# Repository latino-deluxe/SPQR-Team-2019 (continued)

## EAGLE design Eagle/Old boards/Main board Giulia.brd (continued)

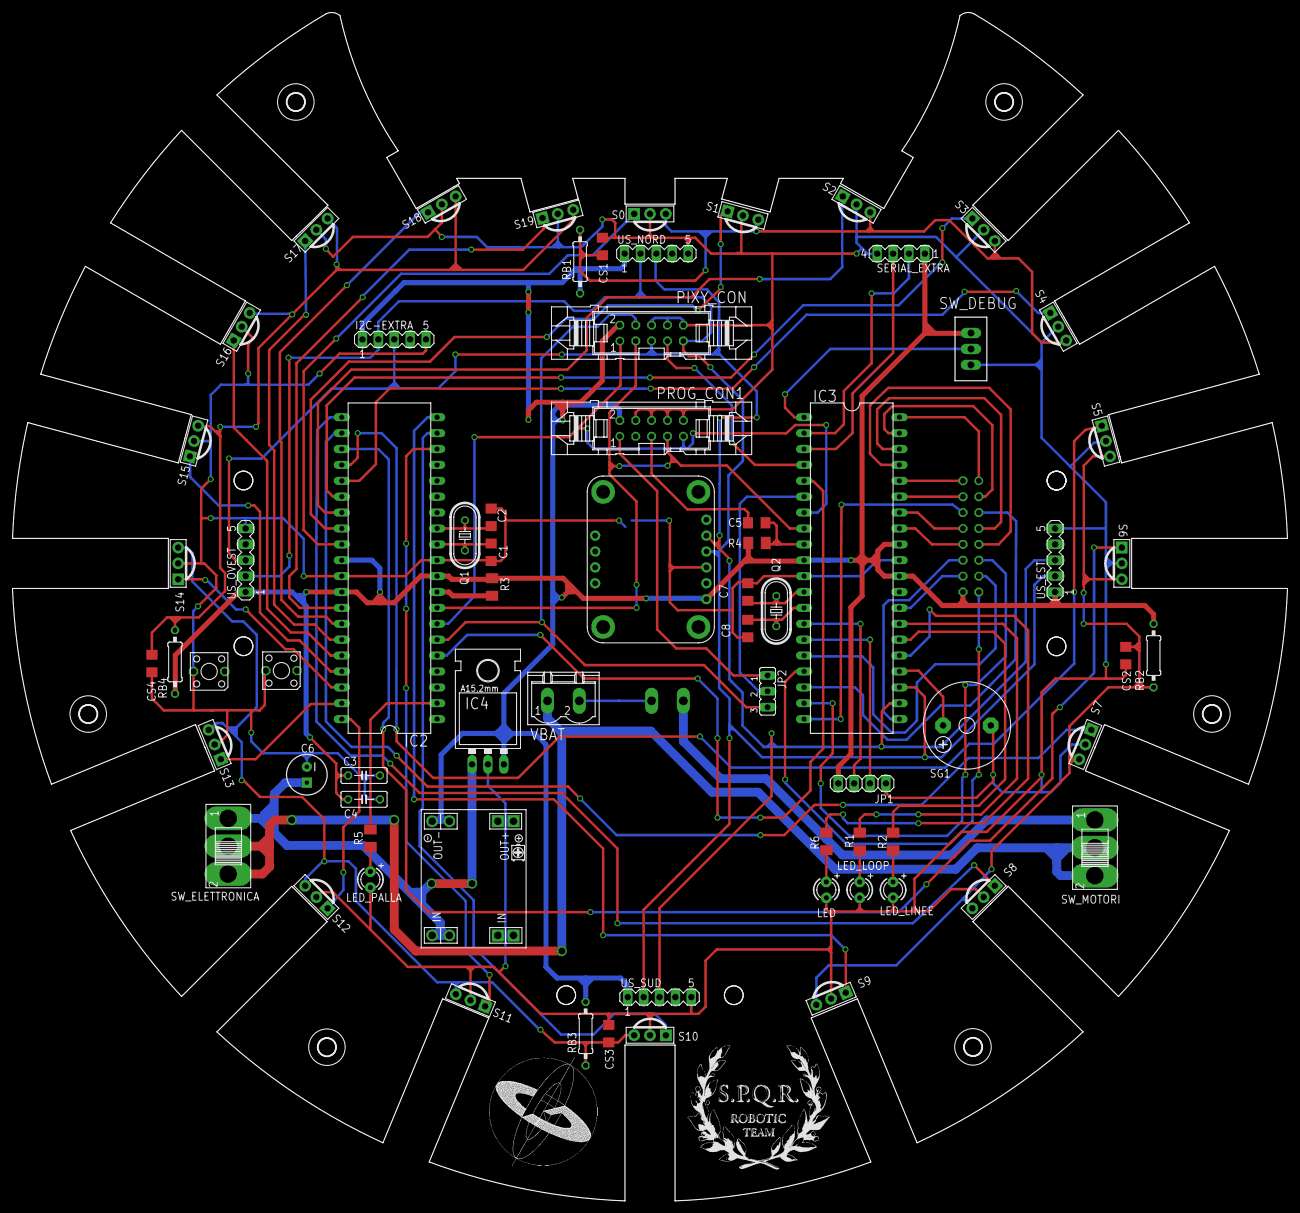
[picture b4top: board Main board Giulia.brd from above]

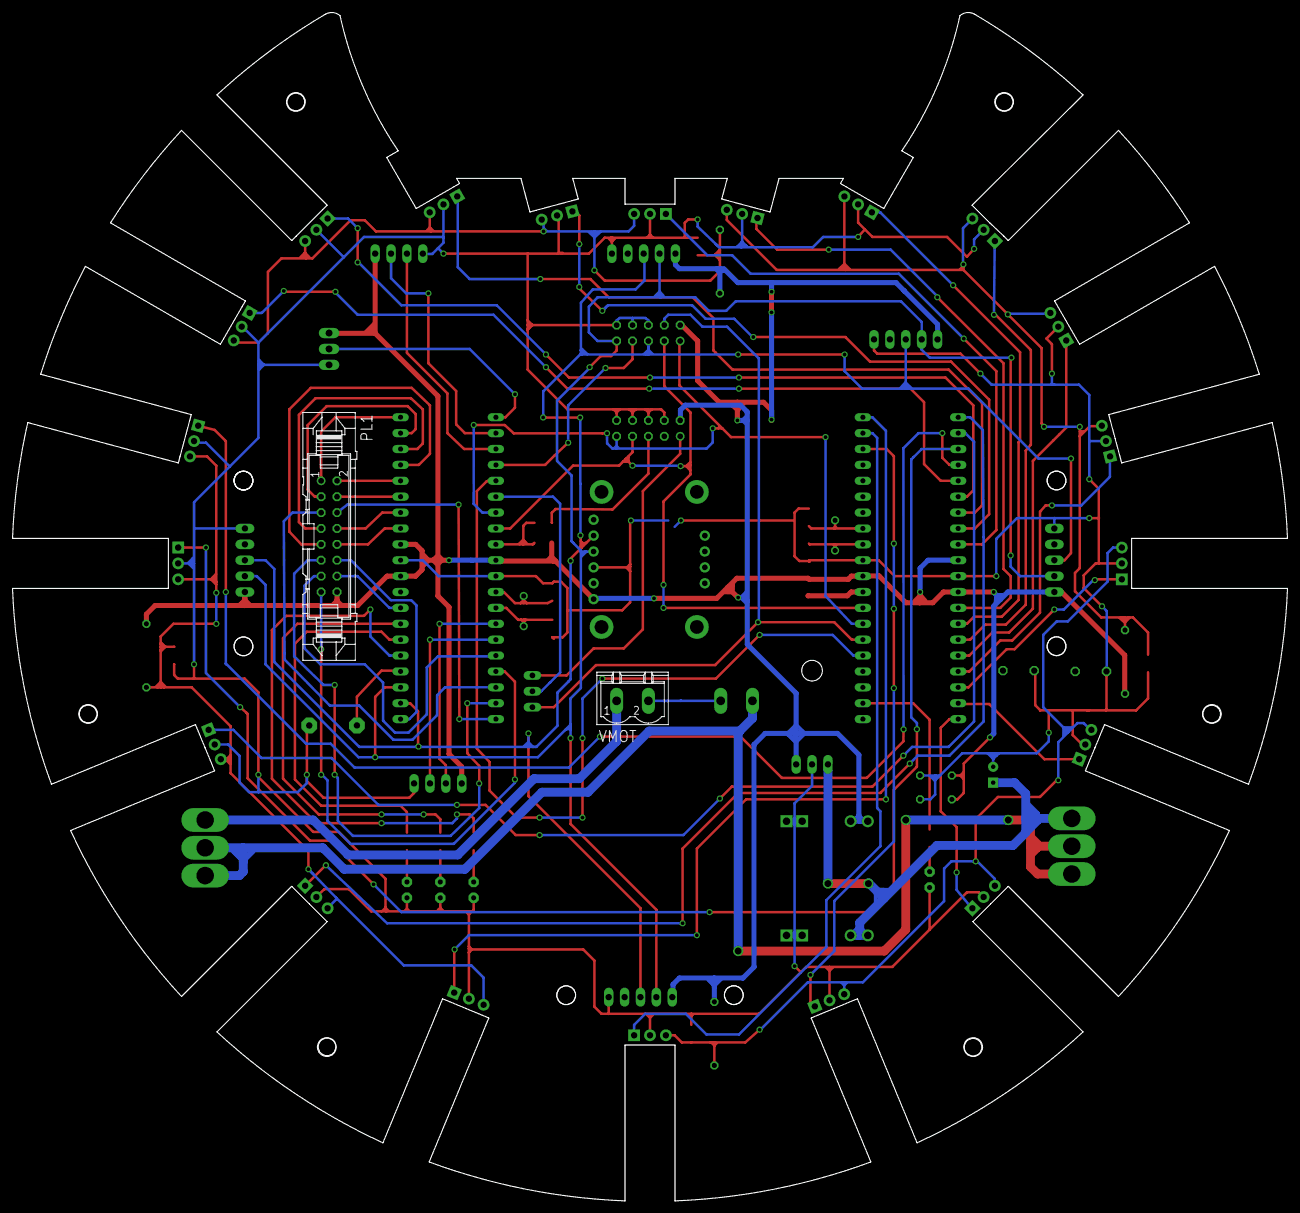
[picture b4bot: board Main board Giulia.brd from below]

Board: 2 copper layers, 203.8 x 190.0 mm, 78 parts (2 on the bottom side), 74 nets.

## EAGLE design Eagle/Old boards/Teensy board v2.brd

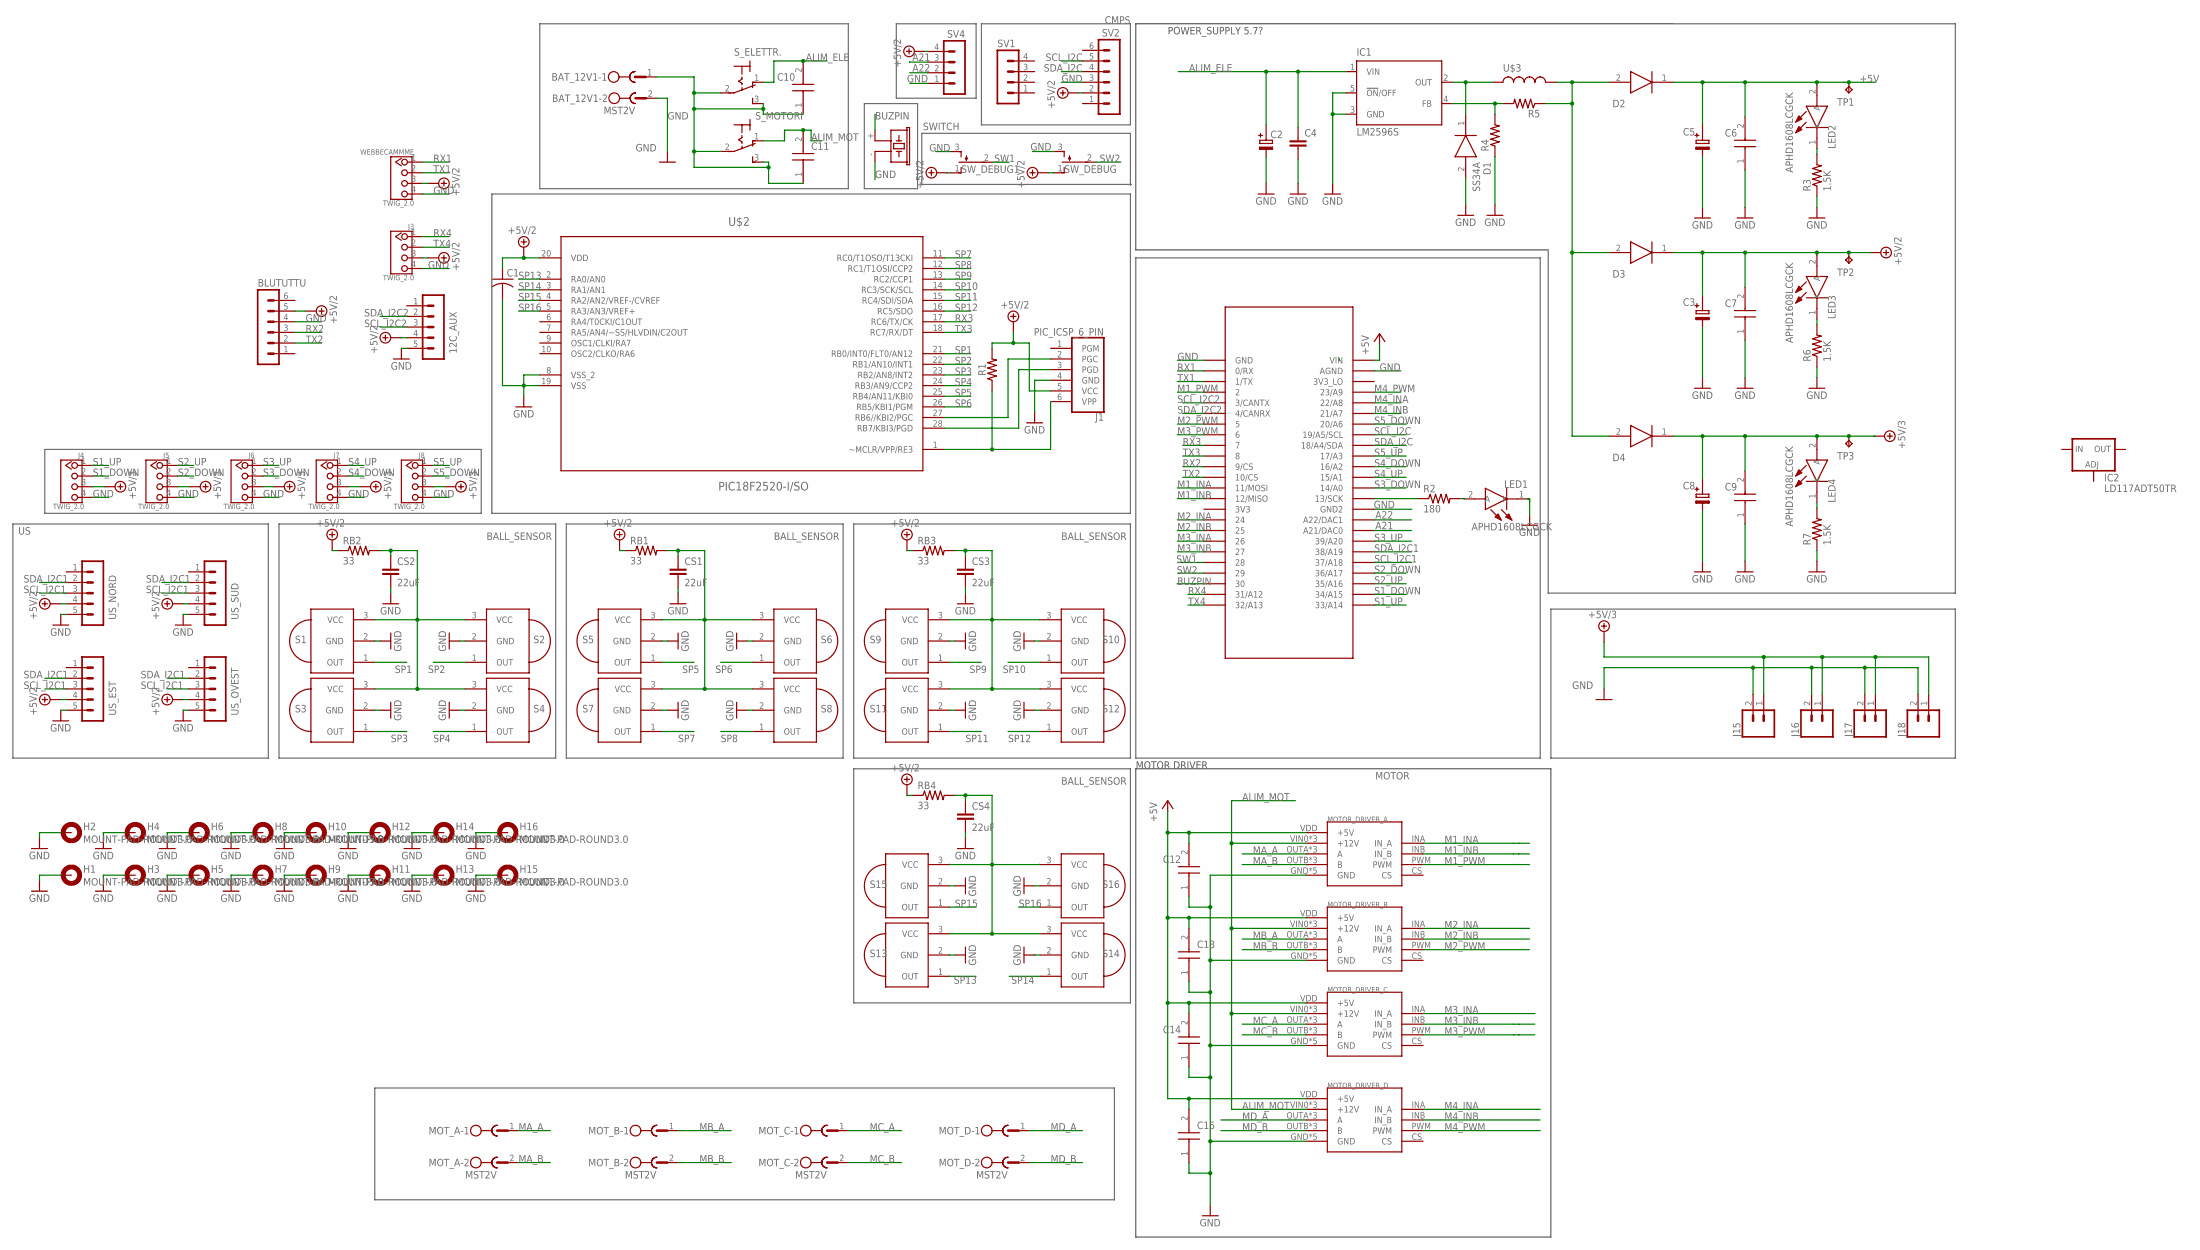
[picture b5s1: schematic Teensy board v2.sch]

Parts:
12C_AUX: MA05-1
BAT_12V1: MST2V; MSTBV2
BLUTUTTU: MA06-1
C1: C-USC1206; C1206
C2, C3, C5, C8: C-PR-SMD-SV-E/F; SV-E/F
C4: CC1206; C1206
C6, C7, C9, C10, C11, C12, C13, C14, C15: 12065D106KAT2A; CAPC3216X229N
CS1, CS2, CS3, CS4: 22uF; C1206
D1: SS34A; DIOM5026X262N
D2, D3, D4: SE20FG-M3_H; SODFL3718X108N
H1, H2, H3, H4, H5, H6, H7, H8, H9, H10, H11, H12, H13, H14, H15, H16: MOUNT-PAD-ROUND3.0; 3,0-PAD
IC1: LM2596S; TO263-5
IC2: LD117ADT50TR; DPACK
J1: PIC_ICSP_6_PIN; MOLEX-1X6
J3, J4, J5, J6, J7, J8: TWIG_2.0; 2.0_1X4
J15, J16, J17, J18: CONN_02; 1X02
LED1, LED2, LED3, LED4: APHD1608LCGCK; LEDM168X80N
MOTOR_DRIVER_A: VNH5019
MOTOR_DRIVER_B: VNH5019
MOTOR_DRIVER_C: VNH5019
MOTOR_DRIVER_D: VNH5019
MOT_A: MST2V; MSTBV2
MOT_B: MST2V; MSTBV2
MOT_C: MST2V; MSTBV2
MOT_D: MST2V; MSTBV2
R1: 10k; M1206
R2: 180; M1206
R3, R6, R7: 1.5K; R1206
R4, R5: R-US_R1206; R1206
RB1, RB2, RB3, RB4: 33; M1206
S1, S2, S3, S4, S5, S6, S7, S8, S9, S10, S11, S12, S13, S14, S15, S16: PNA460XM
SG1: F/CM12P
SV1, SV4: MA04-1
SV2: MA06-1
SW_DEBUG, SW_DEBUG1: TL38PO; TL3XPO
S_ELETTR.: 320-916
S_MOTORI: 320-916
TP1, TP2, TP3: TPTP13SQ; TP13SQ
U$1: TEENSY_3.5/3.6
U$2: PIC18F2520-I/SO; SOIC127P1030X265-28N
U$3: MSS1260
US_EST: MA05-1
US_NORD: MA05-1
US_OVEST: MA05-1
US_SUD: MA05-1
WEBBECAMMME: TWIG_2.0; 2.0_1X4

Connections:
5.7V-DIRAMAZIONE2: D2.2 (A), D3.2 (A), D4.2 (A), R5.1, U$3.P$1
+5V: C5.+, C6.2, D2.1 (K), LED2.2 (A), TP1.TP, U$1.VIN
+5V/2: 12C_AUX.4, BLUTUTTU.5, C1.1, C3.+, C7.2, D3.1 (K), J1.5 (VCC), J3.3, LED3.2 (A), R1.2, RB1.1, RB2.1, RB3.1, RB4.1, SV2.2, SV4.4, SW_DEBUG.1 (O), SW_DEBUG1.1 (O), TP2.TP, U$2.20 (VDD), US_EST.4, US_NORD.4, US_OVEST.4, US_SUD.4, WEBBECAMMME.3
+5V/3: C8.+, C9.2, D4.1 (K), J4.3, J5.3, J6.3, J7.3, J8.3, J15.1, J16.1, J17.1, J18.1, LED4.2 (A), TP3.TP
A21: SV4.3, U$1.21/DAC0 (A21/DAC0)
A22: SV4.2, U$1.A22/DAC1
ALIM_ELE: C2.+, C4.1, C10.2, IC1.1 (VIN), S_ELETTR..1 (O)
ALIM_MOT: C11.2, MOTOR_DRIVER_A.VIN0 (+12V), MOTOR_DRIVER_A.VIN1 (+12V), MOTOR_DRIVER_A.VIN2 (+12V), MOTOR_DRIVER_B.VIN0 (+12V), MOTOR_DRIVER_B.VIN1 (+12V), MOTOR_DRIVER_B.VIN2 (+12V), MOTOR_DRIVER_C.VIN0 (+12V), MOTOR_DRIVER_C.VIN1 (+12V), MOTOR_DRIVER_C.VIN2 (+12V), MOTOR_DRIVER_D.VIN0 (+12V), MOTOR_DRIVER_D.VIN1 (+12V), MOTOR_DRIVER_D.VIN2 (+12V), S_MOTORI.1 (O)
BUZPIN: SG1.+ (1), U$1.30
GND: 12C_AUX.5, BAT_12V1.2, BLUTUTTU.4, C1.2, C2.-, C3.-, C4.2, C5.-, C6.1, C7.1, C8.-, C9.1, C12.1, C13.1, C14.1, C15.1, CS1.2, CS2.2, CS3.2, CS4.2, D1.2 (A), H1.B3,0, H2.B3,0, H3.B3,0, H4.B3,0, H5.B3,0, H6.B3,0, H7.B3,0, H8.B3,0, H9.B3,0, H10.B3,0, H11.B3,0, H12.B3,0, H13.B3,0, H14.B3,0, H15.B3,0, H16.B3,0, IC1.3 (GND), IC1.5 (!ON!/OFF), J1.4 (GND), J3.4, J4.4, J5.4, J6.4, J7.4, J8.4, J15.2, J16.2, J17.2, J18.2, LED1.1 (K), MOTOR_DRIVER_A.GND, MOTOR_DRIVER_A.GND0 (GND), MOTOR_DRIVER_A.GND1 (GND), MOTOR_DRIVER_A.GND2 (GND), MOTOR_DRIVER_A.GND3 (GND), MOTOR_DRIVER_B.GND, MOTOR_DRIVER_B.GND0 (GND), MOTOR_DRIVER_B.GND1 (GND), MOTOR_DRIVER_B.GND2 (GND), MOTOR_DRIVER_B.GND3 (GND), MOTOR_DRIVER_C.GND, MOTOR_DRIVER_C.GND0 (GND), MOTOR_DRIVER_C.GND1 (GND), MOTOR_DRIVER_C.GND2 (GND), MOTOR_DRIVER_C.GND3 (GND), MOTOR_DRIVER_D.GND, MOTOR_DRIVER_D.GND0 (GND), MOTOR_DRIVER_D.GND1 (GND), MOTOR_DRIVER_D.GND2 (GND), MOTOR_DRIVER_D.GND3 (GND), R3.1, R4.1, R6.1, R7.1, S1.2 (GND), S2.2 (GND), S3.2 (GND), S4.2 (GND), S5.2 (GND), S6.2 (GND), S7.2 (GND), S8.2 (GND), S9.2 (GND), S10.2 (GND), S11.2 (GND), S12.2 (GND), S13.2 (GND), S14.2 (GND), S15.2 (GND), S16.2 (GND), SG1.- (2), SV2.3, SV4.1, SW_DEBUG.3 (S), SW_DEBUG1.3 (S), U$1.AGND, U$1.GND, U$1.GND2, U$2.8 (VSS_2), U$2.19 (VSS), US_EST.5, US_NORD.5, US_OVEST.5, US_SUD.5, WEBBECAMMME.4
M1_INA: MOTOR_DRIVER_A.INA (IN_A), U$1.11/MOSI
M1_INB: MOTOR_DRIVER_A.INB (IN_B), U$1.12/MISO
M1_PWM: MOTOR_DRIVER_A.PWM, U$1.2
M2_INA: MOTOR_DRIVER_B.INA (IN_A), U$1.24
M2_INB: MOTOR_DRIVER_B.INB (IN_B), U$1.25
M2_PWM: MOTOR_DRIVER_B.PWM, U$1.5
M3_INA: MOTOR_DRIVER_C.INA (IN_A), U$1.26
M3_INB: MOTOR_DRIVER_C.INB (IN_B), U$1.27
M3_PWM: MOTOR_DRIVER_C.PWM, U$1.6
M4_INA: MOTOR_DRIVER_D.INA (IN_A), U$1.22/A8
M4_INB: MOTOR_DRIVER_D.INB (IN_B), U$1.21/A7
M4_PWM: MOTOR_DRIVER_D.PWM, U$1.23/A9
MA_A: MOTOR_DRIVER_A.OUTA (A), MOTOR_DRIVER_A.OUTA2 (A), MOTOR_DRIVER_A.OUTA3 (A), MOT_A.1
MA_B: MOTOR_DRIVER_A.OUTB (B), MOTOR_DRIVER_A.OUTB1 (B), MOTOR_DRIVER_A.OUTB3 (B), MOT_A.2
MB_A: MOTOR_DRIVER_B.OUTA (A), MOTOR_DRIVER_B.OUTA2 (A), MOTOR_DRIVER_B.OUTA3 (A), MOT_B.1
MB_B: MOTOR_DRIVER_B.OUTB (B), MOTOR_DRIVER_B.OUTB1 (B), MOTOR_DRIVER_B.OUTB3 (B), MOT_B.2
MC_A: MOTOR_DRIVER_C.OUTA (A), MOTOR_DRIVER_C.OUTA2 (A), MOTOR_DRIVER_C.OUTA3 (A), MOT_C.1
MC_B: MOTOR_DRIVER_C.OUTB (B), MOTOR_DRIVER_C.OUTB1 (B), MOTOR_DRIVER_C.OUTB3 (B), MOT_C.2
MD_A: MOTOR_DRIVER_D.OUTA (A), MOTOR_DRIVER_D.OUTA2 (A), MOTOR_DRIVER_D.OUTA3 (A), MOT_D.1
MD_B: MOTOR_DRIVER_D.OUTB (B), MOTOR_DRIVER_D.OUTB1 (B), MOTOR_DRIVER_D.OUTB3 (B), MOT_D.2
unnamed: J1.6 (VPP), R1.1, U$2.1 (~MCLR/VPP/RE3)
unnamed: J1.3 (PGD), U$2.28 (RB7/KBI3/PGD)
unnamed: J1.2 (PGC), U$2.27 (RB6//KBI2/PGC)
unnamed: R2.1, U$1.13/SCK
unnamed: LED1.2 (A), R2.2
unnamed: C12.2, C13.2, C14.2, C15.2, D1.1 (K), IC1.2 (OUT), MOTOR_DRIVER_A.VDD (+5V), MOTOR_DRIVER_B.VDD (+5V), MOTOR_DRIVER_C.VDD (+5V), MOTOR_DRIVER_D.VDD (+5V), U$3.P$2
unnamed: IC1.4 (FB), R4.2, R5.2
unnamed: LED2.1 (K), R3.2
unnamed: LED3.1 (K), R6.2
unnamed: LED4.1 (K), R7.2
unnamed: BAT_12V1.1, C10.1, C11.1, S_ELETTR..2, S_ELETTR..3 (S), S_MOTORI.2, S_MOTORI.3 (S)
POWER_BLOK_1: CS1.1, RB1.2, S5.3 (VCC), S6.3 (VCC), S7.3 (VCC), S8.3 (VCC)
POWER_BLOK_2: CS2.1, RB2.2, S1.3 (VCC), S2.3 (VCC), S3.3 (VCC), S4.3 (VCC)
POWER_BLOK_3: CS3.1, RB3.2, S9.3 (VCC), S10.3 (VCC), S11.3 (VCC), S12.3 (VCC)
POWER_BLOK_4: CS4.1, RB4.2, S13.3 (VCC), S14.3 (VCC), S15.3 (VCC), S16.3 (VCC)
RX1: U$1.0/RX, WEBBECAMMME.1
RX2: BLUTUTTU.3, U$1.9/CS
RX3: U$1.7, U$2.17 (RC6/TX/CK)
RX4: J3.1, U$1.31/A12
S1_DOWN: J4.2, U$1.34/A15
S1_UP: J4.1, U$1.33/A14
S2_DOWN: J5.2, U$1.36/A17
S2_UP: J5.1, U$1.35/A16
S3_DOWN: J6.2, U$1.14/A0
S3_UP: J6.1, U$1.39/A20
S4_DOWN: J7.2, U$1.16/A2
S4_UP: J7.1, U$1.15/A1
S5_DOWN: J8.2, U$1.20/A6
S5_UP: J8.1, U$1.17/A3
SCL_I2C: SV2.5, U$1.19/A5/SCL
SCL_I2C1: U$1.37/A18, US_EST.3, US_NORD.3, US_OVEST.3, US_SUD.3
SCL_I2C2: 12C_AUX.3, U$1.3/CANTX
SDA_I2C: SV2.4, U$1.18/A4/SDA
SDA_I2C1: U$1.38/A19, US_EST.2, US_NORD.2, US_OVEST.2, US_SUD.2
SDA_I2C2: 12C_AUX.2, U$1.4/CANRX
SP1: S1.1 (OUT), U$2.21 (RB0/INT0/FLT0/AN12)
SP2: S2.1 (OUT), U$2.22 (RB1/AN10/INT1)
SP3: S3.1 (OUT), U$2.23 (RB2/AN8/INT2)
SP4: S4.1 (OUT), U$2.24 (RB3/AN9/CCP2)
SP5: S5.1 (OUT), U$2.25 (RB4/AN11/KBI0)
SP6: S6.1 (OUT), U$2.26 (RB5/KBI1/PGM)
SP7: S7.1 (OUT), U$2.11 (RC0/T1OSO/T13CKI)
SP8: S8.1 (OUT), U$2.12 (RC1/T1OSI/CCP2)
SP9: S9.1 (OUT), U$2.13 (RC2/CCP1)
SP10: S10.1 (OUT), U$2.14 (RC3/SCK/SCL)
SP11: S11.1 (OUT), U$2.15 (RC4/SDI/SDA)
SP12: S12.1 (OUT), U$2.16 (RC5/SDO)
SP13: S13.1 (OUT), U$2.2 (RA0/AN0)
SP14: S14.1 (OUT), U$2.3 (RA1/AN1)
SP15: S15.1 (OUT), U$2.4 (RA2/AN2/VREF-/CVREF)
SP16: S16.1 (OUT), U$2.5 (RA3/AN3/VREF+)
SW1: SW_DEBUG1.2, U$1.28
SW2: SW_DEBUG.2, U$1.29
TX1: U$1.1/TX, WEBBECAMMME.2
TX2: BLUTUTTU.2, U$1.10/CS
TX3: U$1.8, U$2.18 (RC7/RX/DT)
TX4: J3.2, U$1.32/A13

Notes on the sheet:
CMPS
BALL_SENSOR
MOTOR
SWITCH
POWER_SUPPLY 5.7?
MOTOR DRIVER

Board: 2 copper layers, 113 parts (29 on the bottom side), 87 nets, no tracks yet.

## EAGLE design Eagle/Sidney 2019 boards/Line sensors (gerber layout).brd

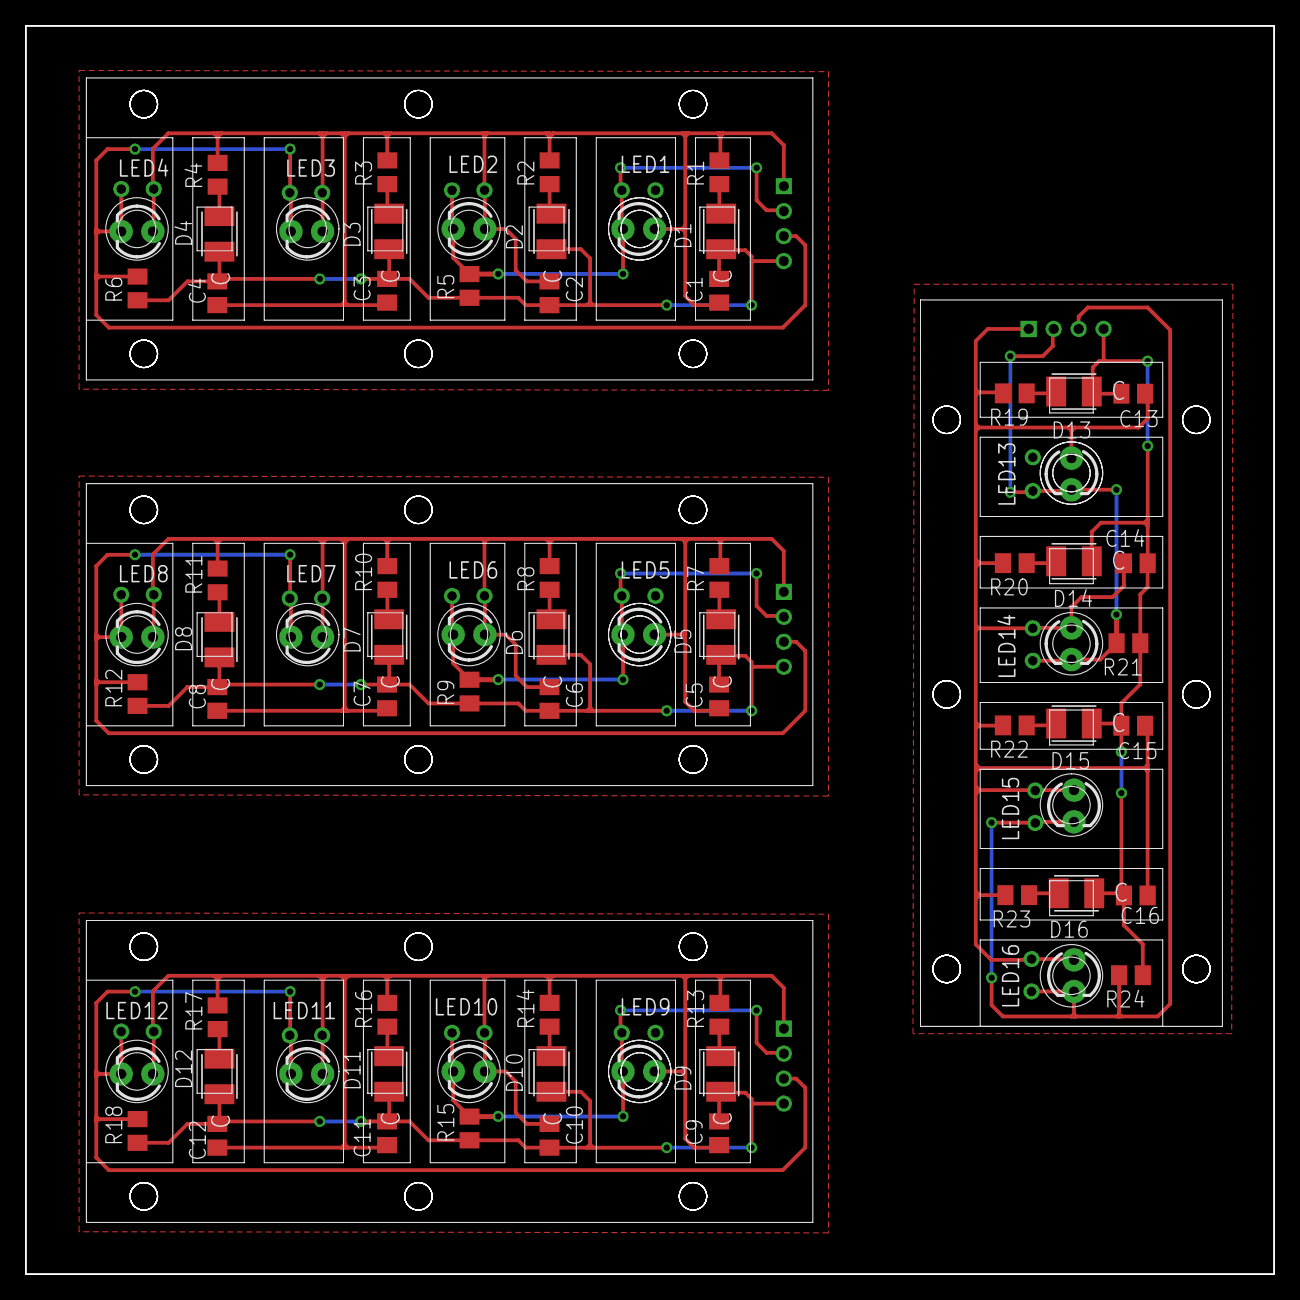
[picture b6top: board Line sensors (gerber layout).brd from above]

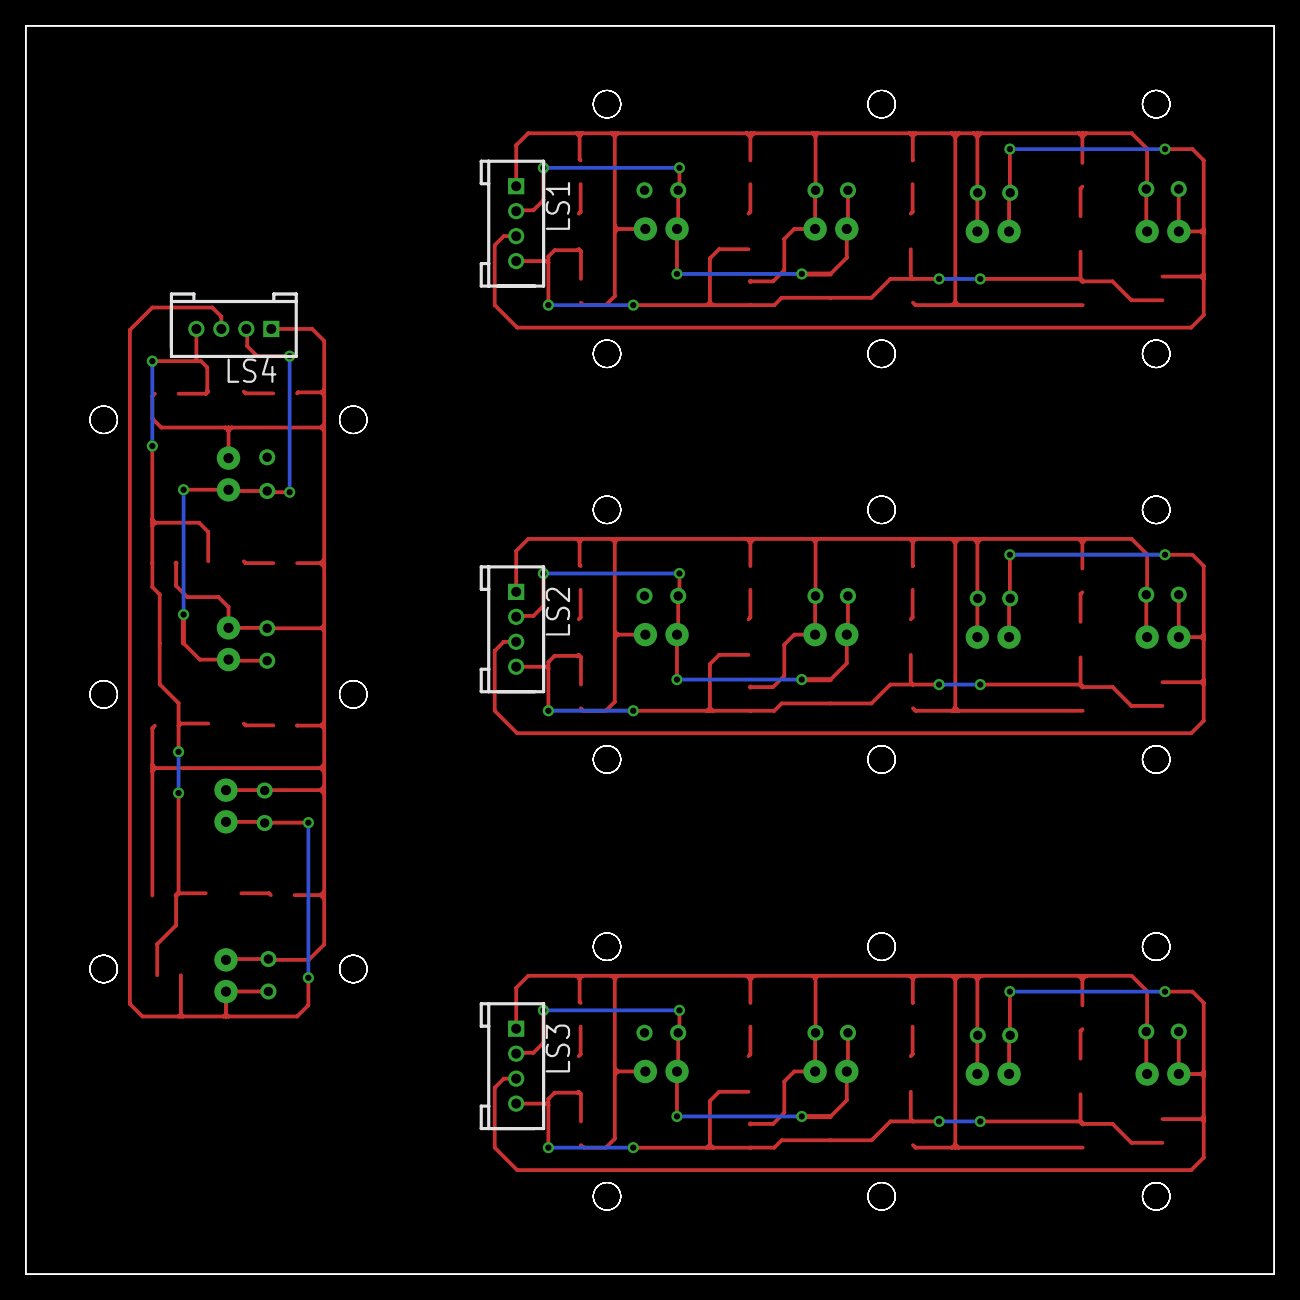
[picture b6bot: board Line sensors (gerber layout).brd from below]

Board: 2 copper layers, 100.0 x 100.0 mm, 76 parts (4 on the bottom side), 32 nets.

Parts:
C1, C2, C3, C4, C5, C6, C7, C8, C9, C10, C11, C12, C13, C14, C15, C16: 100n; M0805
D1, D2, D3, D4, D5, D6, D7, D8, D9, D10, D11, D12, D13, D14, D15, D16: 3528-2PIN
LED1, LED2, LED3, LED4, LED5, LED6, LED7, LED8, LED9, LED10, LED11, LED12, LED13, LED14, LED15, LED16: LED3MM
LS1, LS2, LS3, LS4: 4P-2.0
R1, R2, R3, R4, R7, R8, R10, R11, R13, R14, R16, R17, R19, R20, R22, R23: 330; M0805
R5, R6, R9, R12, R15, R18, R21, R24: 10k; M0805

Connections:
5V: C1.2, C2.2, C3.2, C4.2, LED1.A, LED2.A, LED3.A, LED4.A, LS1.1, R1.2, R2.2, R3.2, R4.2
5V1: C5.2, C6.2, C7.2, C8.2, LED5.A, LED6.A, LED7.A, LED8.A, LS2.1, R7.2, R8.2, R10.2, R11.2
5V2: C9.2, C10.2, C11.2, C12.2, LED9.A, LED10.A, LED11.A, LED12.A, LS3.1, R13.2, R14.2, R16.2, R17.2
5V3: C13.2, C14.2, C15.2, C16.2, LED13.A, LED14.A, LED15.A, LED16.A, LS4.1, R19.2, R20.2, R22.2, R23.2
GND: C1.1, C2.1, C3.1, C4.1, D1.1, D2.1, D3.1, D4.1, LS1.4, R5.1, R6.1
GND1: C5.1, C6.1, C7.1, C8.1, D5.1, D6.1, D7.1, D8.1, LS2.4, R9.1, R12.1
GND2: C9.1, C10.1, C11.1, C12.1, D9.1, D10.1, D11.1, D12.1, LS3.4, R15.1, R18.1
GND3: C13.1, C14.1, C15.1, C16.1, D13.1, D14.1, D15.1, D16.1, LS4.4, R21.1, R24.1
unnamed: D5.2, R7.1
unnamed: D6.2, R8.1
unnamed: D1.2, R1.1
unnamed: D2.2, R2.1
unnamed: D7.2, R10.1
unnamed: D8.2, R11.1
unnamed: D9.2, R13.1
unnamed: D10.2, R14.1
unnamed: D11.2, R16.1
unnamed: D12.2, R17.1
unnamed: D3.2, R3.1
unnamed: D13.2, R19.1
unnamed: D14.2, R20.1
unnamed: D4.2, R4.1
unnamed: D15.2, R22.1
unnamed: D16.2, R23.1
SIG1: LED1.K, LED2.K, LS1.2, R5.2
SIG2: LED3.K, LED4.K, LS1.3, R6.2
SIG3: LED5.K, LED6.K, LS2.2, R9.2
SIG4: LED7.K, LED8.K, LS2.3, R12.2
SIG5: LED9.K, LED10.K, LS3.2, R15.2
SIG6: LED11.K, LED12.K, LS3.3, R18.2
SIG7: LED13.K, LED14.K, LS4.2, R21.2
SIG8: LED15.K, LED16.K, LS4.3, R24.2

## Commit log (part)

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2019-02-27 Fixato che sono una capra e metto parentesi alla fallo di fido
2019-02-27 space_invaders_3 carino :D
2019-02-27 space_invaders_idea_3_carino_2
2019-02-27 Goalie con palla dietro, linee meh
2019-02-27 Vedi changelog, importante
2019-03-04 New center_goal_post, ema testalo please
2019-03-04 handleInterruptEasy, ematino prova pure questo please
2019-03-04 impostata HandIntEasy
2019-03-04 Prova nuovo interrupt (funziona da dio) ma da sistemare
2019-03-05 fixato delay nell'interrupt, da provare
2019-03-06 MANUAL MERGE NEWCODE2 TO MASTER
2019-03-06 MANUAL MERGE NEWCODE 2 TO MASTER
2019-03-06 Fixed a problem with getSensorIndex that caused general mess
2019-03-06 fixato storcimento, dichiaro concluso goalie. devo offrire caffè al prof
2019-03-06 test switch
2019-03-06 portiere carino, da aggiungere menamoli e fixare un paio di bug
2019-03-08 tracciamento centro porta
2019-03-08 implementata camera in routine di gioco, da testare e perfezionare
2019-03-09 commenti e appunti
2019-03-10 inclusa nella routine di gioco comunicazione, strategia, programma BT
2019-03-11 space_invaders_3+space_invaders_m. no palla dietro, fix
2019-03-11 merge2
2019-03-11 merge3
2019-03-11 space_invaders_storce?
2019-03-11 portierino carino :D
2019-03-11 menamoli approssimato (wannabe) :D
2019-03-16 vecchio sistema di storcimento camera da testare
2019-03-17 added bluetooth example code
2019-03-18 Fix goalie per portiere, no pallaDietroP
2019-03-18 Preparazione uso bluetooth
2019-03-18 correz. fascia che non legge non funziona
2019-03-19 inizio bluetooth-ino
2019-03-20 space_invaders_camera da testare
2019-03-20 cambio ruolo BT
2019-03-20 iytuyg
2019-03-20 puppa
2019-03-20 ciao
2019-03-20 space_invaders_camera_migliorato
2019-03-24 reintrodotte note e canzoncine, start e stop setup, grandi classici
2019-03-25 sistemati file music
2019-03-25 space_invaders_us se camera morta
2019-03-25 SUPERSTORCIMENTO
2019-03-25 atom non salva, l'animaccia sua
2019-03-25 implementazione menamoli, da finire
2019-03-26 blinktest avr12
2019-03-26 Tweak space_invaderozzo
2019-03-26 menamoli bello funzionante :D (timeout da fare)
2019-03-26 fpos
2019-03-27 inizio funzioni test by siria, loop infinito
2019-03-27 eoooooo da siria
2019-03-27 test menu belli
2019-03-28 Provato un fix per goalie in space_invaders, da testare su campo :D
2019-03-28 fix goalie in space invaders
2019-03-28 storcimentoZone
2019-03-28 keeper min&max
2019-03-28 bip bop atom non salva
2019-03-28 integrazione comrade in switch ruoli
2019-03-28 fix reintrodotto menamoli, goalie da space_invaders non funonzia
2019-03-28 goalie era imploso ma i vecchi commit ci salvano
2019-03-28 nuovi angoli goalie belli funzionanti
2019-03-28 space_invaders_imploso
2019-03-29 Fix per space_invaders_us, zona posteriore rimpicciolita, camera da zero
2019-03-29 kepalle
2019-03-29 space_invaders_vivo_evvaiiiiiiiiiiii_senza_us_solo_camera
2019-03-29 prima partita penosa
2019-03-29 interrupt post partita persa
2019-03-29 schifo
2019-03-29 space_invaders_us_funge_bene
2019-03-29 bello
2019-03-29 fine seconda gara 9-7 per noi, biascica impazzisce linee BT da sistemare
2019-04-01 Diminuita drasticamente attesa una volta presa la linea
2019-04-01 attese minori
2019-04-01 new portierino
2019-04-01 new portierino_2
2019-04-01 robe
2019-04-01 TEST CAMERA
2019-04-02 tutto bene tranne linee 10:54
2019-04-02 pre partita catania lego
2019-04-02 prima partita 9a0, pre seconda partita
2019-04-02 modifica alle linee fighe, romecup a domani
2019-04-03 Sono una capra e inverto le direzioni (sens 18)
2019-04-03 post partita Kilohertz 11-1
2019-04-03 limite portiere us
2019-04-03 attaccante fighissimo
2019-04-03 P a 1.7 e D a 5 :)
2019-04-03 post amichevole 5-1 tempo singolo, sistemato autogoal (mortacci mia)
2019-04-04 controllo palla linee
2019-04-04 prepartita gigahertz oh fuck
2019-04-04 secondo tempo gigahertz
2019-04-04 correzione brutto bug con le linee, mannagia a me -emaletta
2019-04-05 pre finale
2019-04-05 pre secondo tempo finale
2019-04-09 TeensyThreads. esempio in utility :)
2019-04-10 PWM motori a 15kHz!!!
2019-04-11 Threads! Scritti i principali, riordinato il codice. Da ottimizzare.
2019-04-16 velocità corrette portiere, da ricalibrare tutto
2019-04-16 prove
2019-04-17 cartella hardware, foto
2019-04-17 Test storcimento
2019-04-17 sistemato storcimento e nuovo pid, da ritarare i valori
2019-04-23 impostate variabili volatili imu ma nulla, decidere se riscrivere
2019-04-23 test
2019-04-24 Aggiunto thread, sistemato codice as usual
2019-04-24 piccoli cambiamenti stupidi da aereoporto
2019-04-30 Fixati dei bug, sistemate robe, come al solito
2019-05-01 Commit aereo. Tutto nei thread, da testare in lab.
2019-05-02 interrupt sistemato, no thread routine
2019-05-02 tante robe! pid semi calibrato e thread buoni
2019-05-06 storcimento funziona! bomba!!!
2019-05-08 aggiunti file al branch
2019-05-08 push instructions
2019-05-08 git test
2019-05-08 gisus
2019-05-08 changes in thread
2019-05-08 File fusion
2019-05-09 slight improvements on the top PCB
2019-05-10 pre-partita kazaki
2019-05-10 pre-partita kazaki 2
2019-05-10 added LM2940 library
2019-05-10 pre-partita kazaki 4
2019-05-10 partita disastrosa. riscrivere codice robot nuovo
2019-05-13 added motor board schematic
2019-05-13 added supply switches to motor board
2019-05-13 supply improvements in motor board
2019-05-13 auto login test
2019-05-13 finished motor drivers (schematic)
2019-05-13 completed motor board schematic
2019-05-13 added motor board DXF file
2019-05-13 storcimento meh ma meglio
2019-05-14 began supply circuit
2019-05-14 added line sensors schematic and board
2019-05-15 damn vs_code files
2019-05-15 mannaggia
2019-05-15 storcimento incrementale bello :D
2019-05-15 deleted useless save files
2019-05-15 cosine storcimento
2019-05-15 Started implementing camera for logic zone
2019-05-17 completed supply and component list for motor board
2019-05-17 fixed some missing traces
2019-05-20 Fix protocollo camera e storcimento
2019-05-21 removed old save files
2019-05-21 added old boards for parts
2019-05-21 Finished uC board (fixed supply to give infrared and US sensors stable 5V)
2019-05-21 Began components list for uC board
2019-05-21 Finished motor board, deleted useless files, added parts in components lists for both boards and other stuff
2019-05-22 Fixed line sensors issue
2019-05-22 Added grove connectors for auxiliary supply
2019-05-22 Deleted useless files
2019-05-22 Almost completed components lists
2019-05-22 Fix nuova posizione, funzionano sia camera che US
2019-05-22 nuovo pinout scheda
2019-05-22 Finished RS components lists
2019-05-22 Fixed error on uC board
2019-05-22 se si tratta di andare dritti siamo a cavallo
2019-05-22 Fixed polygon near battery causing a short circuit
2019-05-23 Started working on line sensors's 3.3V supply
2019-05-23 Removed old files and gerber generation tests, added Giulia main board (for SPQR and school's symbols)
2019-05-23 Fixed motor driver pin hardly connected to ground
2019-05-23 Created DXFs, PDFs and PNGs, small improvements to line sensors board
2019-05-24 Made hole smaller to have bigger top ground plane on motor board
2019-05-24 Created line sensors layout for gerber generation. Added logos to uC and motor PCBs. Generater and uploaded on PCBWAY every gerber
2019-05-26 Movimento sull'asse annullato dai sensori linea
2019-05-26 tolti messaggi di debug
2019-05-27 New ball reading code. in utility
2019-05-27 movimento bono
2019-05-27 pinout linesensor, board non funzionano
2019-06-04 AOOO FUNZIA BYTE UNITO
2019-06-05 AO S'ACCENNE E FUZNONAAAAAAAAA (CAMERA E LINEE, LA BUSSOLA ROVESCIATA DA UN VALORE ATTORNO AI 200 ALL'ACCENSIONE)
2019-06-05 New shields. Working 4 motors
2019-06-06 Remap bussola funzionante
2019-06-06 improved non-working ball_read
2019-06-07 Added issues list, fixed uC board short to ground
2019-06-07 pin corretti motori
2019-06-07 linee da sistemare com non va
2019-06-07 linee migliorate! ordinate, niente flag
2019-06-07 Working code for ball sensors read and teensy-pro_mini communication
2019-06-07 è nato Furio! insegue la palla, linee ottime
2019-06-08 aggiunta playsafe, gioco sensori esterni e interni
2019-06-08 dato porta specchio da provare, portiere
2019-06-08 ultimo commit giuro
2019-06-09 opssss
2019-06-10 Now ball-read is using registers instead of digitalRead
2019-06-10 dumb coso
2019-06-10 camera non funziona
2019-06-10 ball read nano interpolation, switches to turn serial communication on on teensy
2019-06-10 fix ball_read_nano
2019-06-10 Camera serial comm. working, data managing to be fixed
2019-06-10 linee a cavallo fixate
2019-06-10 Robot gioca con interpolazione, da sistemare il passaggio del dato della distanza
2019-06-11 Fixed ball reading from teensy. Distance now working
2019-06-11 Fixed values for ball nano
2019-06-11 Added boards PDFs for documentation
2019-06-11 please stop fixing this thing
2019-06-11 storcimento quasi funziona, partita con biascica
2019-06-11 movimento ok, storcimento no
2019-06-12 Even more cleaning
2019-06-12 70 esco a sinistra 170 destra
2019-06-12 70sx 170 dx
2019-06-12 Fix storcimento
2019-06-12 portiere buonino
2019-06-12 Starting implementing logic zone
2019-06-12 Attaccante e portiere con US
2019-06-12 Post partita, esce ogni tanto e prende male palla
2019-06-13 storcimento ABBASTANZA funzionante
2019-06-13 big problemozzo di motori fuori asse
2019-06-13 storcimento carino
2019-06-14 Storcimento nuovo!
2019-06-14 Partita, bug linee storcimento strano
2019-06-17 tolta roba
2019-06-17 Storcimento funzionante (veramente questa volta)
2019-06-17 movimento da migliorare
2019-06-17 linee più sensibili
2019-06-17 gioco buono camera da testare7
2019-06-17 Camera buona movimento ritarare
2019-06-17 Mask funz da sistemare TANTO
2019-06-18 added differences between angles
2019-06-18 Uscita buona con palla che ferma
2019-06-18 fixCamImu for zone matrix using camera
2019-06-18 starting implementing zone using camera, to be continued
2019-06-19 THREADS!
2019-06-21 zone (x axis) with camera
2019-06-21 linee molto meglio
2019-06-21 gioca benino, qualche presa si perde la palla
2019-06-21 added bt_test
2019-06-21 final bible draft (read heckinbible.odt)
2019-06-21 zone us funzionanti, da provare il mix di tutti
2019-06-23 added frontpage without team photo and tidied up the folders
2019-06-24 Movimento buono
2019-06-24 zone using camera and lines, started writing a keeper
2019-06-24 Funziona ma non so perchè
2019-06-24 nice portierozzo
2019-06-24 even nicer portierino
2019-06-24 Va di merda controlla commit prec
2019-06-25 pippo pluto e paperino
2019-06-25 Reading ball distance using counter highest value, works like a charm
2019-06-25 fixed power supply and misc errors, added main flowchart, todo on zenhub
2019-06-25 utility bluetooth
2019-06-25 comrade funge, zona compagno con bluetooth da finire di testare
2019-06-26 Terzultimo giorno
2019-06-26 cleaning ball_read
2019-06-26 Rambogit add .
2019-06-26 ball_read only with interpolation
2019-06-26 added page numbers (heckinbiblepag.pdf/.odt) and misc pics
2019-06-26 Attacantino e test
2019-06-26 Funziona meh da rivedere domani, ritoccare movimento
2019-06-27 Movimento buono, vel 350+
2019-06-27 all in one test for us sensors
2019-06-27 aggiunto test us per il piccolo dario che non sa cambiare branch
2019-06-27 Added US tool
2019-06-27 completed bible (heckinbiblepag.pdf) and started portfolio
2019-06-27 fixati bug con il linesensbyte=15 e gestitito caso 15, esco poco
2019-06-27 comunicazione emrbionale con un po' di gap
2019-06-27 continuing portfolio, halp
2019-06-27 added triangle frames and continued the portfolio (don't need in but keep it)
2019-06-28 Poster almost finished
2019-06-28 finally, bible. added the all left format (heckinbiblepagALLLEFT.pdf. choose what to print and have a nice journey
2019-06-28 Poster done
2019-06-28 pecette
2019-07-15 post robocup2019 code
2019-07-22 Gioco con palla open, TC
2019-10-21 bug ridefinizione costante note b1 e file header mancante di versione precedente
2019-10-28 fixing an import
2019-10-28 Codice ritarato campo nuovo
2019-10-29 force merge from org
2019-10-29 storcimento carino funzionante, da sistemare gli angoli di presa palla probabilmente
2019-10-30 AAANGOLO
2019-11-07 Aggiunto schema linearita' motori7
2019-11-11 Remap pwm
2019-11-11 Aumento deadzone rispetto alla perfezione più assoluta, visto che non viviamo in un mondo ideale
2019-11-11 Storcimento con movimento buoni
